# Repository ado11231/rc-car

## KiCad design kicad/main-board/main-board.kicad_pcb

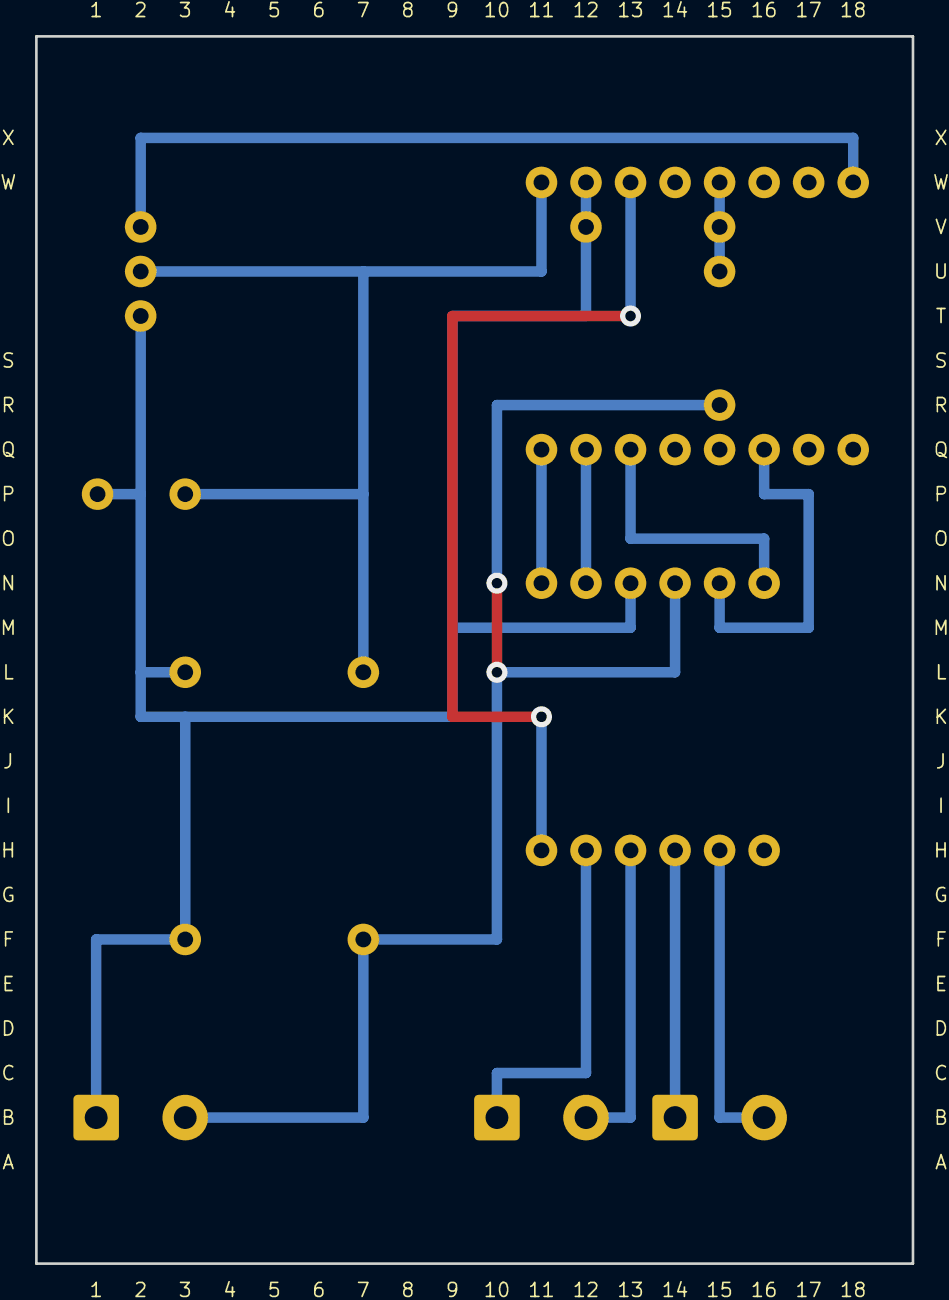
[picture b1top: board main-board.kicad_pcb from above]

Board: 2 copper layers, 50.0 x 70.0 mm, 12 parts (0 on the bottom side), 14 nets.

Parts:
C1: 470uF; CP_Radial_D8.0mm_P5.00mm
J1: BATTERY; TerminalBlock_Phoenix_MKDS-1,5-2-5.08_1x02_P5.08mm_Horizont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
J2: LEFT MOTOR; TerminalBlock_Phoenix_MKDS-1,5-2-5.08_1x02_P5.08mm_Horizont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
J3: RIGHT MOTOR; TerminalBlock_Phoenix_MKDS-1,5-2-5.08_1x02_P5.08mm_Horizont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
J4: SERVO; PinHeader_1x03_P2.54mm_Horizontal
R1: 47k; R_Axial_DIN0207_L6.3mm_D2.5mm_P7.62mm_Horizontal
R2: 10k; R_Axial_DIN0207_L6.3mm_D2.5mm_P7.62mm_Horizontal
U1A, U1B: ESP32-C3; PinSocket_1x08_P2.54mm_Vertical
U2A, U2B: HW-627; PinSocket_1x06_P2.54mm_Vertical
U3: Mini360

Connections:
+3V3: U1B.3V3, U2B.EEP
+5V: C1.+, J4.5V, U1B.5V, U3.OUT+
BATT_SENSE: R1.2, R2.1, U1B.G3
GND: C1.-, J1.-, J4.GND, R2.2, U1B.GND, U2A.GND, U3.IN-, U3.OUT-
IN1: U1A.G7, U2A.IN1
IN2: U1A.G10, U2A.IN2
IN3: U1A.G6, U2A.IN3
IN4: U1A.G5, U2A.IN4
OUT1: J2.1, U2B.OUT1
OUT2: J2.2, U2B.OUT2
OUT3: J3.1, U2B.OUT3
OUT4: J3.2, U2B.OUT4
SERVO_SIG: J4.SIG, U1B.G0
VBAT: J1.+, R1.1, U2A.VCC, U3.IN+
